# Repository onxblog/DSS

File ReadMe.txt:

### ----- Digital Soldering Station ----- ###

This station designed in Ukraine and in code have Ukrainian annotation.
Digital Soldering Station (next DSS) designed for iron solder HAKKO 936
Compatible with Lukey 868 852D+ 936+ irons and many others builded on ceramic HAKKO A1321 part.  
DSS have 3 digit led display, buzzer, soft start, programm detector activity, user profilies, encoder managment interface. 

SRC coded in CodeVisionAVR
Firmware autor Victor_P Ukraine

### --- Russian
Данная станция создавалась при участии форума радиокот.
Проект получился весьма интересным и очень качественным.
Дабы труды которые были потраченны на создание данной станции не были напрасны.
Я решил выложить исходные коды (любезно предоставленные Виктором П. во всеобщее пользование) 
и все имеющиеся у меня мои наработки по этой станции во всеобщее пользование.
Особая благодарность Виктору П. за разработку прошивки для данной станции.
Автор прошивки более не поддерживает эту версию станции, а занялся новым проектом совмещающим все имеющиеся у него наработки для создания
новой универсальной станции для всех типов паяльников. Поэтому дання версия отныне в руках GitHub комьюнити.
Версия платы разработанная мною в Eagle, расчитана на паяльники с разъемом вида PS2 от компании Lukey.
Рекомендую прочесть инструкцию, что бы увидеть какой огромный функционал имеет дання станция.
Данные паяльники HAKKO 936 по сей день остаются весьма популярны по причине дешевых расходников и наличия медных жал.
И довольно качесивенного 60Ват керамического нагревателя.

Технические характеристики: 
 Диапазон поддерживаемых температур – 80-420°C.
 Алгоритм нагрева – ПИ.
 Таймер дежурного режима и выключения – есть, совмещенный настраиваемый.
 Программный детектор активности паяльника – есть, настраиваемый.
 Количество профилей паяльников – 2.
 Количество предварительно установленных температур от 3 до 8, настраиваемые.
 Программная калибровка – есть.
 Плавный разогрев – есть.

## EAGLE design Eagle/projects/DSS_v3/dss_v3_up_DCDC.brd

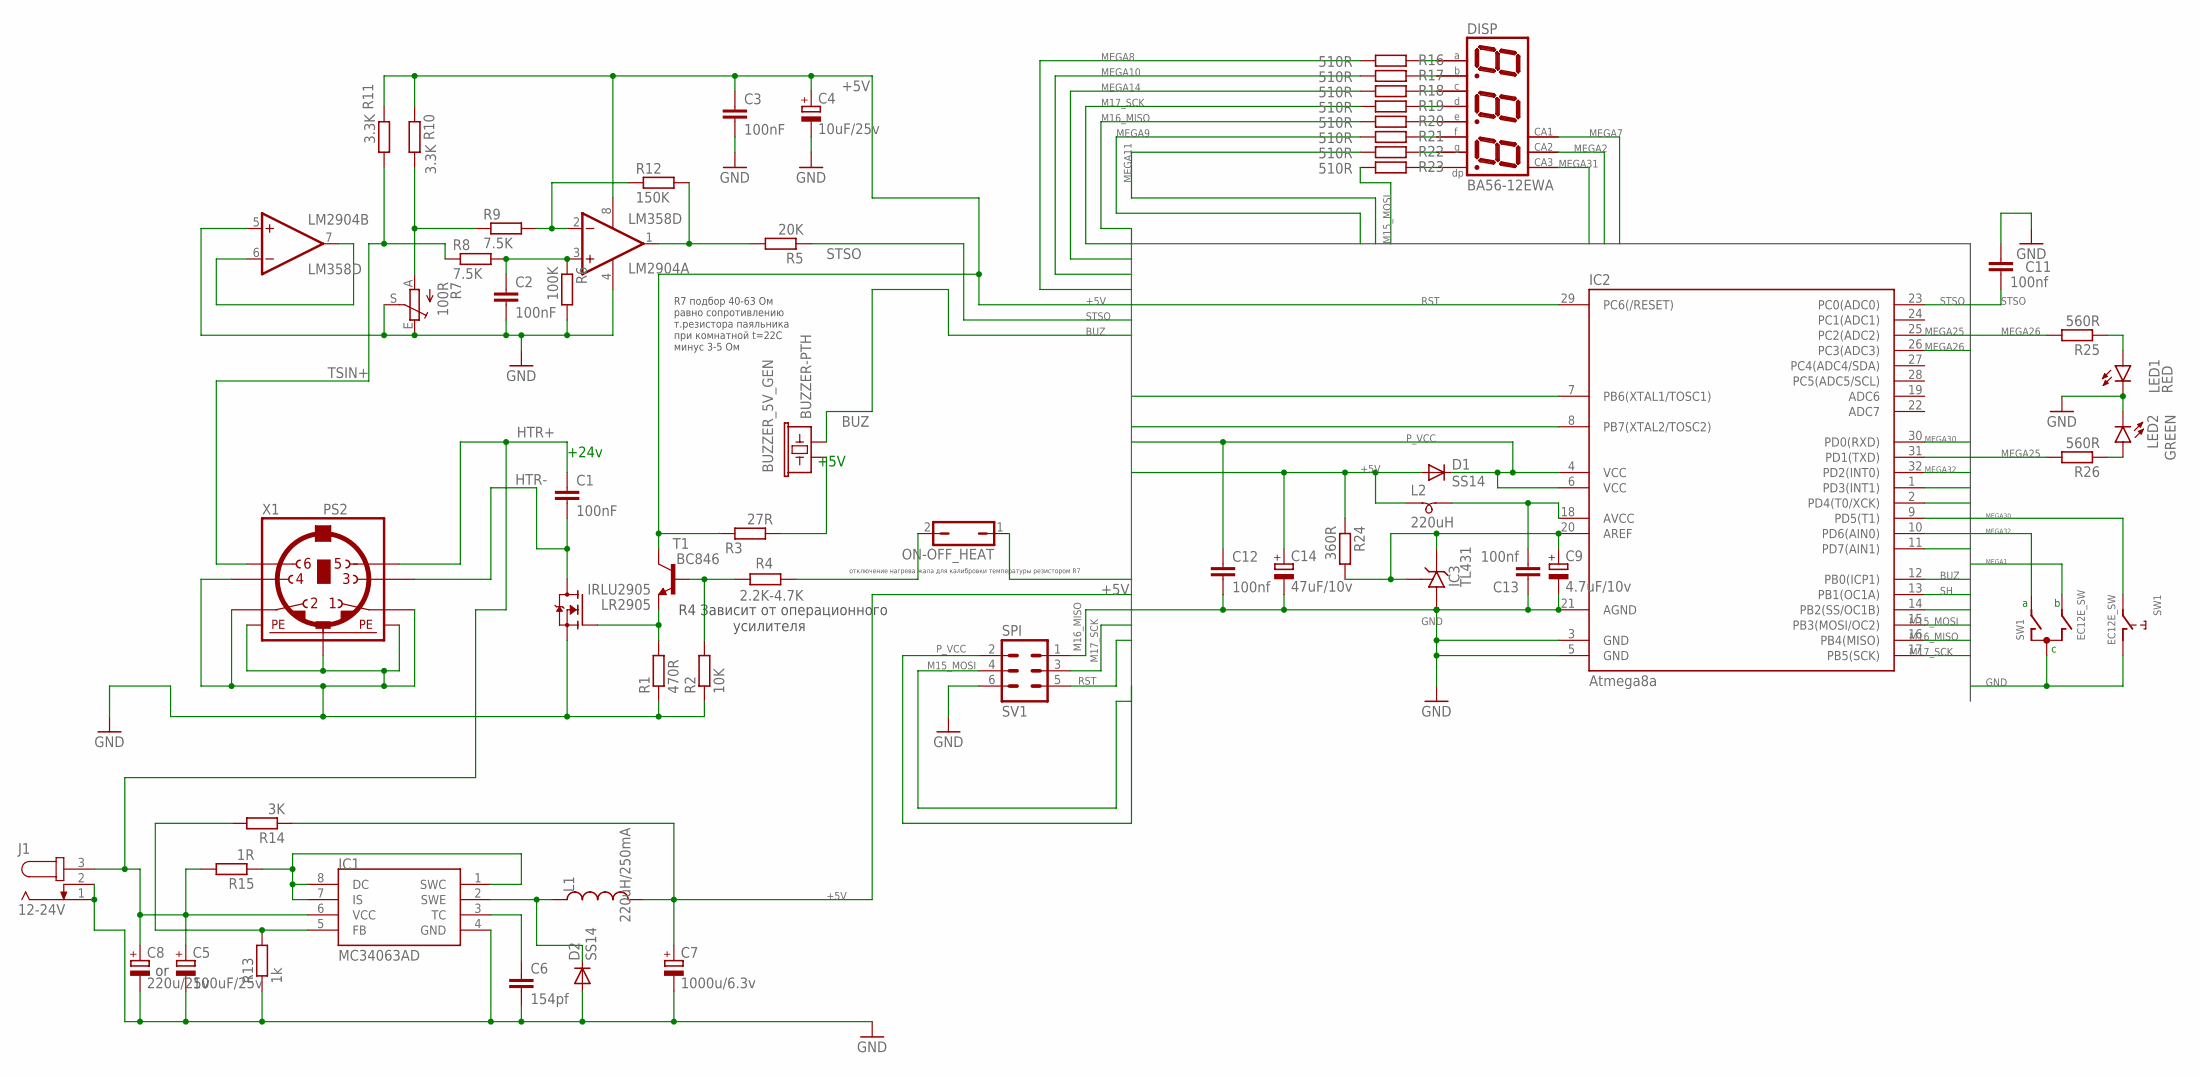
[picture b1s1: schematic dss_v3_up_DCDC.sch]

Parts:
BUZZER_5V_GEN: BUZZER-PTH; BUZZER-12MM
C1, C2, C3: 100nF; C0805
C4: 10uF/25v; CT3528
C5: 100uF/25v; CT6032
C6: 154pf; C0805
C7: 1000u/6.3v; E3,5-8
C8: 220u/25v; E3,5-8
C9: 4.7uF/10v; CT3216
C11, C12, C13: 100nf; C0805
C14: 47uF/10v; CT3528
D1, D2: SS14; DO214AC
DISP: BA56-12EWA; BX56-12
IC1: MC34063AD; SOIC8
IC2: Atmega8a; TQFP32-08
IC3: TL431; SOT23
IRLU2905: LR2905; TO252
J1: 12-24V; SPC4077
L1: 220uH/250mA; L4532P
L2: 220uH; SM-B5
LED1: RED; CHIP-LED0805
LED2: GREEN; CHIP-LED0805
LM2904: LM358D; SO08
ON-OFF_HEAT: JP1Q; JP1
R1: 470R; R0805
R2: 10K; R0805
R3: 27R; R0805
R4: 2.2K-4.7K; R0805
R5: 20K; R0805
R6: 100K; R0805
R7: 100R; B25P
R8, R9: 7.5K; R0805
R10, R11: 3.3K; R0805
R12: 150K; R0805
R13: 1k; R0805
R14: 3K; R0805
R15: 1R; R0805
R16, R17, R18, R19, R20, R21, R22, R23: 510R; R0805
R24: 360R; R0805
R25, R26: 560R; R0805
SV1: SPI; ML6
SW1: EC12E_SW; ALPS_EC12E_SW
T1: BC846; SOT23
X1: PS2; M_DIN6

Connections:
+5V: C3.1, C4.+, C7.+, C14.+, D1.A, L1.2, L2.1, LM2904.8 (V+), R3.2, R10.1, R11.1, R14.1, R24.1, T1.3 (C)
BUZ: BUZZER_5V_GEN.- (2), IC2.12 (PB0(ICP1))
GND: C2.2, C3.2, C4.-, C5.-, C6.2, C7.-, C8.-, C9.-, C11.1, C12.2, C13.1, C14.-, D2.A, IC1.4 (GND), IC2.3 (GND), IC2.5 (GND), IC2.21 (AGND), IC3.3 (A), IRLU2905.3 (S), J1.1, J1.2, LED1.C, LED2.C, LM2904.4 (V-), LM2904.5 (+IN), R1.1, R2.1, R6.2, R7.E, R7.S, R13.1, SV1.6, SW1.C, SW1.D (1), X1.1, X1.2, X1.5, X1.SH1 (PE1), X1.SH2 (PE2), X1.SH3 (PE3)
HTR+: C1.1, C5.+, C8.+, IC1.6 (VCC), J1.3, R15.2, X1.6
HTR-: C1.2, IRLU2905.4 (D), X1.3
M15_MOSI: IC2.15 (PB3(MOSI/OC2)), R23.2, SV1.4
M16_MISO: IC2.16 (PB4(MISO)), R20.2, SV1.1
M17_SCK: IC2.17 (PB5(SCK)), R19.2, SV1.3
MEGA1: IC2.1 (PD3(INT1)), SW1.B
MEGA2: DISP.9 (CA), IC2.2 (PD4(T0/XCK))
MEGA7: DISP.12 (CA), IC2.7 (PB6(XTAL1/TOSC1))
MEGA8: IC2.8 (PB7(XTAL2/TOSC2)), R16.2
MEGA9: IC2.9 (PD5(T1)), R21.2
MEGA10: IC2.10 (PD6(AIN0)), R17.2
MEGA11: IC2.11 (PD7(AIN1)), R22.2
MEGA14: IC2.14 (PB2(SS/OC1B)), R18.2
MEGA25: IC2.25 (PC2(ADC2)), R26.2
MEGA26: IC2.26 (PC3(ADC3)), R25.2
MEGA30: IC2.30 (PD0(RXD)), SW1.E (2)
MEGA31: DISP.8 (CA), IC2.31 (PD1(TXD))
MEGA32: IC2.32 (PD2(INT0)), SW1.A
unnamed: DISP.11 (A), R16.1
unnamed: LED1.A, R25.1
unnamed: DISP.7 (B), R17.1
unnamed: DISP.4 (C), R18.1
unnamed: C9.+, IC2.20 (AREF), IC3.1 (C), IC3.2 (R), R24.2
unnamed: LM2904.1 (OUT), R5.2, R12.2
unnamed: LM2904.6 (-IN), LM2904.7 (OUT)
unnamed: LM2904.2 (-IN), R9.2, R12.1
unnamed: R7.A, R9.1, R10.2
unnamed: IRLU2905.1 (G), R1.2, T1.2 (E)
unnamed: C2.1, LM2904.3 (+IN), R6.1, R8.2
unnamed: DISP.2 (D), R19.1
unnamed: R2.2, R4.2, T1.1 (B)
unnamed: DISP.1 (E), R20.1
unnamed: LED2.A, R26.1
unnamed: BUZZER_5V_GEN.+ (1), R3.1
unnamed: ON-OFF_HEAT.2, R4.1
unnamed: IC1.5 (FB), R13.2, R14.2
unnamed: DISP.10 (F), R21.1
unnamed: DISP.5 (G), R22.1
unnamed: DISP.3 (DP), R23.1
unnamed: IC1.1 (SWC), IC1.7 (IS), IC1.8 (DC), R15.1
unnamed: C13.2, IC2.18 (AVCC), L2.2
unnamed: D2.C, IC1.2 (SWE), L1.1
unnamed: C6.1, IC1.3 (TC)
P_VCC: C12.1, D1.C, IC2.4 (VCC), IC2.6 (VCC), SV1.2
RST: IC2.29 (PC6(/RESET)), SV1.5
SH: IC2.13 (PB1(OC1A)), ON-OFF_HEAT.1
STSO: C11.2, IC2.23 (PC0(ADC0)), R5.1
TSIN+: R8.1, R11.2, X1.8

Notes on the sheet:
R7 подбор 40-63 Ом равно сопротивлению т.резистора паяльника при комнатной t=22С минус 3-5 Ом
+5V
+24v
отключение нагрева жала для калибровки температуры резистором R7
R4 Зависит от операционного усилителя

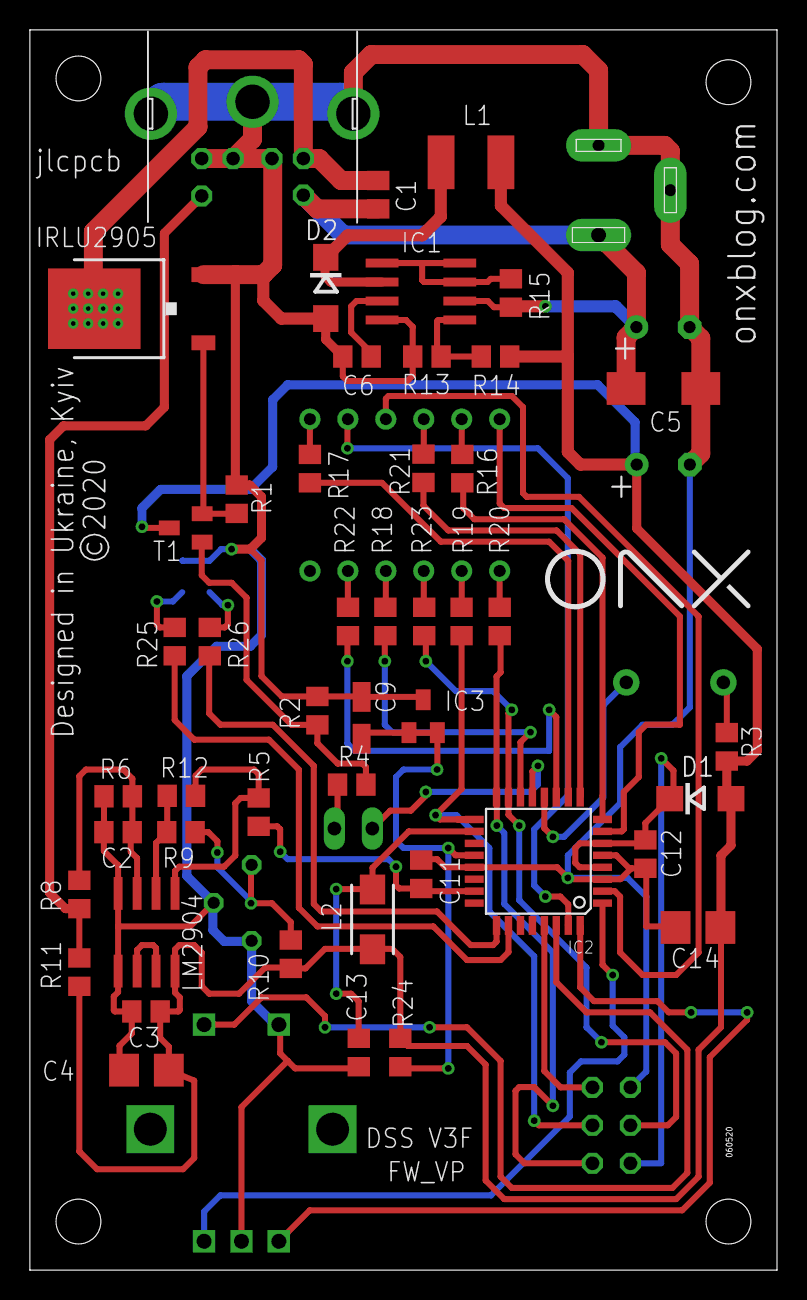
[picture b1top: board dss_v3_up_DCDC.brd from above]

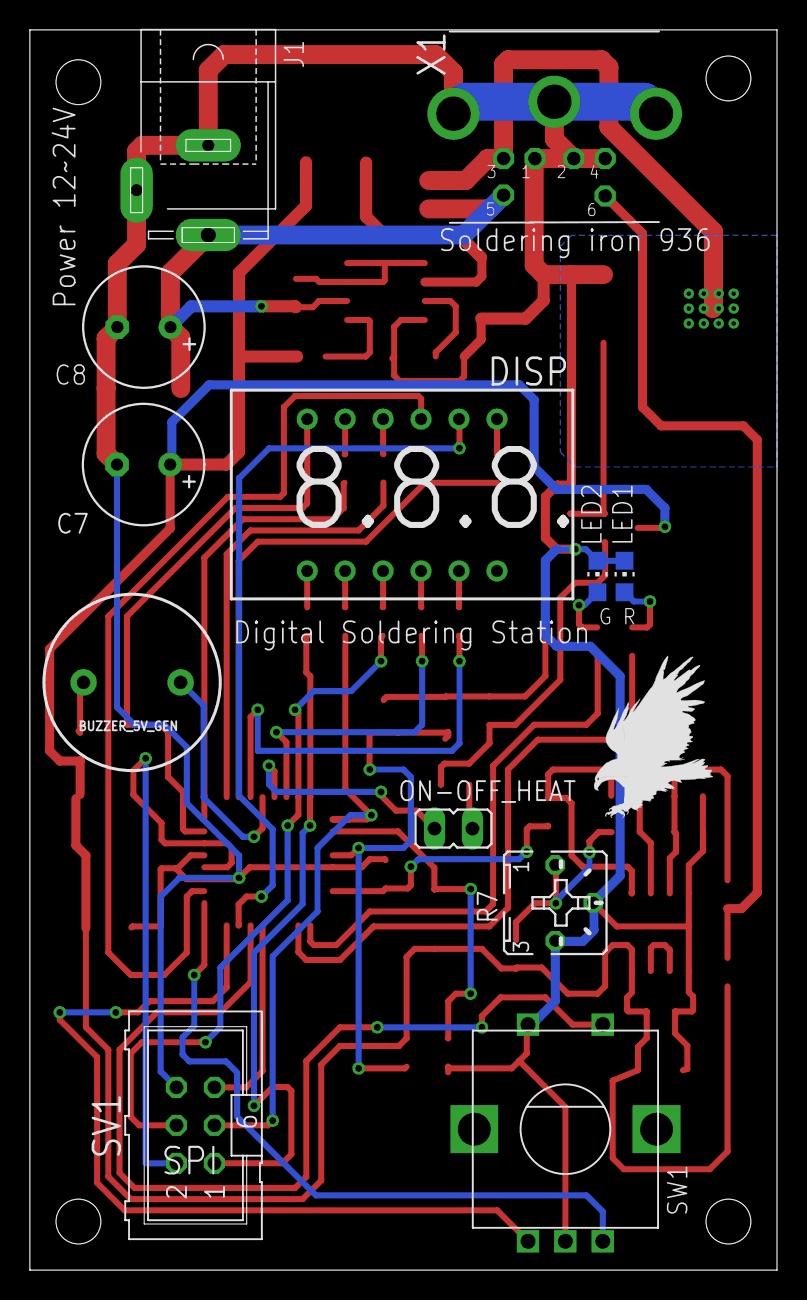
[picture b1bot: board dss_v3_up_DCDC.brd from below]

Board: 2 copper layers, 50.0 x 83.0 mm, 60 parts (13 on the bottom side), 51 nets.

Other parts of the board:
U$2: ONX
U$3: EAGLE-PLC-8MM

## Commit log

2020-04-14 DSS_v3
    First push
2020-04-15 add_img
2020-04-15 new_files
2020-04-15 add img top
2020-04-27 new_board
2020-04-29 gnd fix add smd capacitor for select
2020-05-10 case
2020-05-10 text
2020-05-12 update_location

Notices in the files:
Eagle/projects/DSS_v3/dss_v3_up_DCDC.brd:
©2020
parts and their libraries:
SparkFun-Electromechanical: Licensing: Creative Commons ShareAlike 4.0 International - https://creativecommons.org/licenses/by-sa/4.0
